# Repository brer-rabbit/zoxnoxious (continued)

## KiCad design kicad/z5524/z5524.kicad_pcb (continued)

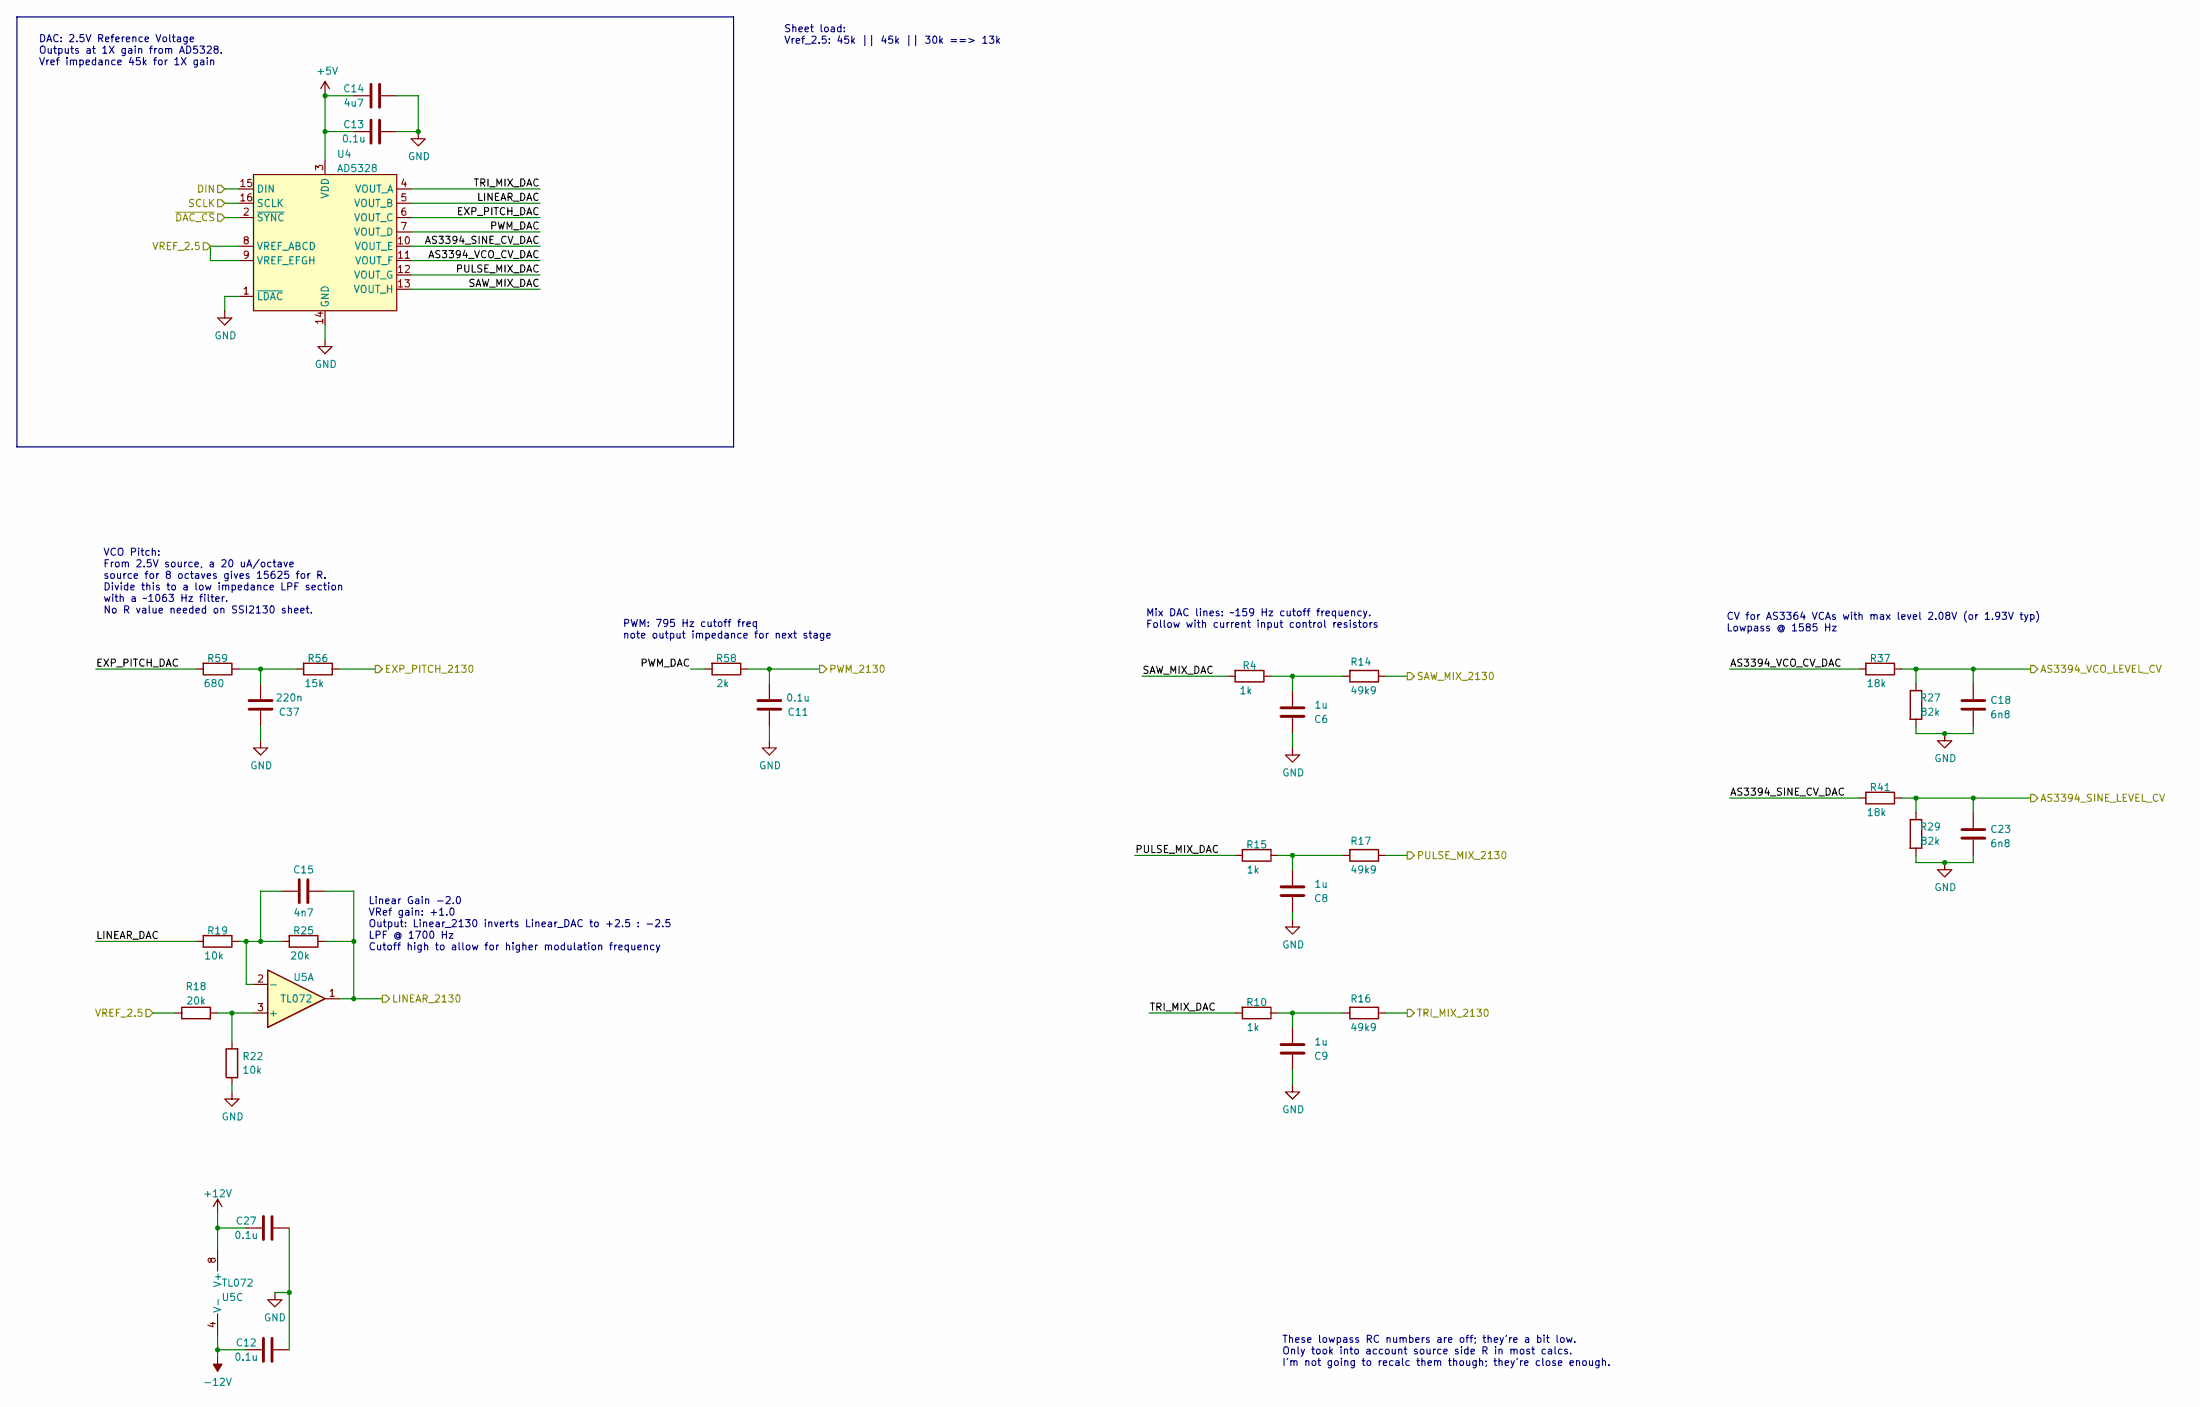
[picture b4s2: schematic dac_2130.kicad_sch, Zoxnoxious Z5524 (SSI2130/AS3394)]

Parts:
C6, C8, C9: 1u; C_0603_1608Metric; LCSC C15849
C11, C12, C13, C27: 0.1u; C_0603_1608Metric; LCSC C14663
C14: 4u7; C_0603_1608Metric; LCSC C19666
C15: 4n7; C_0603_1608Metric; LCSC C53987
C18, C23: 6n8; C_0603_1608Metric; LCSC C1631
C37: 220n; C_0603_1608Metric; LCSC C21120
R4, R10, R15: 1k; R_0603_1608Metric; LCSC C21190
R14, R16, R17: 49k9; R_0603_1608Metric; LCSC C23184
R18, R25: 20k; R_0603_1608Metric; LCSC C4184
R19, R22: 10k; R_0603_1608Metric; LCSC C25804
R27, R29: 82k; R_0603_1608Metric; LCSC C23254
R37, R41: 18k; R_0603_1608Metric; LCSC C25810
R56: 15k; R_0603_1608Metric; LCSC C22809
R58: 2k; R_0603_1608Metric; LCSC C22975
R59: 680; R_0603_1608Metric; LCSC C23228
U4: AD5328; TSSOP-16_4.4x5mm_P0.65mm; LCSC C29162
U5: TL072; SO-8_3.9x4.9mm_P1.27mm; LCSC C6961

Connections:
+5V: C13.1, C14.1, U4.3 (VDD); also elsewhere on the board
+12V: C27.1, U5.8 (V+); also elsewhere on the board
-12V: C12.1, U5.4 (V-); also elsewhere on the board
/AS3394_MOD_CV: C18.1, R27.1, R37.1; also elsewhere on the board
/AS3394_SINE_CV: C23.1, R29.1, R41.1; also elsewhere on the board
/DAC 2130/AS3394_SINE_CV_DAC: R41.2, U4.10 (VOUT_E)
/DAC 2130/AS3394_VCO_CV_DAC: R37.2, U4.11 (VOUT_F)
/DAC 2130/EXP_PITCH_2130: R56.1; also elsewhere on the board
/DAC 2130/EXP_PITCH_DAC: R59.2, U4.6 (VOUT_C)
/DAC 2130/LINEAR_2130: C15.2, R25.1, U5.1; also elsewhere on the board
/DAC 2130/LINEAR_DAC: R19.2, U4.5 (VOUT_B)
/DAC 2130/PULSE_MIX_2130: R17.1; also elsewhere on the board
/DAC 2130/PULSE_MIX_DAC: R15.2, U4.12 (VOUT_G)
/DAC 2130/PWM_2130: C11.1, R58.1; also elsewhere on the board
/DAC 2130/PWM_DAC: R58.2, U4.7 (VOUT_D)
/DAC 2130/SAW_MIX_2130: R14.1; also elsewhere on the board
/DAC 2130/SAW_MIX_DAC: R4.2, U4.13 (VOUT_H)
/DAC 2130/TRI_MIX_2130: R16.1; also elsewhere on the board
/DAC 2130/TRI_MIX_DAC: R10.2, U4.4 (VOUT_A)
/SPI_CLK: U4.16 (SCLK); also elsewhere on the board
/SPI_CS1: U4.2 (~SYNC); also elsewhere on the board
/SPI_MOSI: U4.15 (DIN); also elsewhere on the board
/VREF_2.5: R18.1, U4.8 (VREF_ABCD), U4.9 (VREF_EFGH); also elsewhere on the board
GND: C6.2, C8.2, C9.2, C11.2, C12.2, C13.2, C14.2, C18.2, C23.2, C27.2, C37.2, R22.1, R27.2, R29.2, U4.1 (~LDAC), U4.14 (GND); also elsewhere on the board
unnamed: C6.1, R4.1, R14.2
unnamed: C8.1, R15.1, R17.2
unnamed: C9.1, R10.1, R16.2
unnamed: C37.1, R56.2, R59.1
unnamed: R18.2, R22.2, U5.3 (+)
unnamed: C15.1, R19.1, R25.2, U5.2 (-)

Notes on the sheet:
PWM: 795 Hz cutoff freq note output impedance for next stage
Linear Gain -2.0 VRef gain: +1.0 Output: Linear_2130 inverts Linear_DAC to +2.5 : -2.5 LPF @ 1700 Hz Cutoff high to allow for higher modulation frequency
Mix DAC lines: ~159 Hz cutoff frequency. Follow with current input control resistors
These lowpass RC numbers are off; they're a bit low. Only took into account source side R in most calcs. I'm not going to recalc them though; they're close enough.
CV for AS3364 VCAs with max level 2.08V (or 1.93V typ) Lowpass @ 1585 Hz
VCO Pitch: From 2.5V source, a 20 uA/octave source for 8 octaves gives 15625 for R. Divide this to a low impedance LPF section with a ~1063 Hz filter. No R value needed on SSI2130 sheet.
Sheet load: Vref_2.5: 45k || 45k || 30k ==> 13k
DAC: 2.5V Reference Voltage Outputs at 1X gain from AD5328. Vref impedance 45k for 1X gain

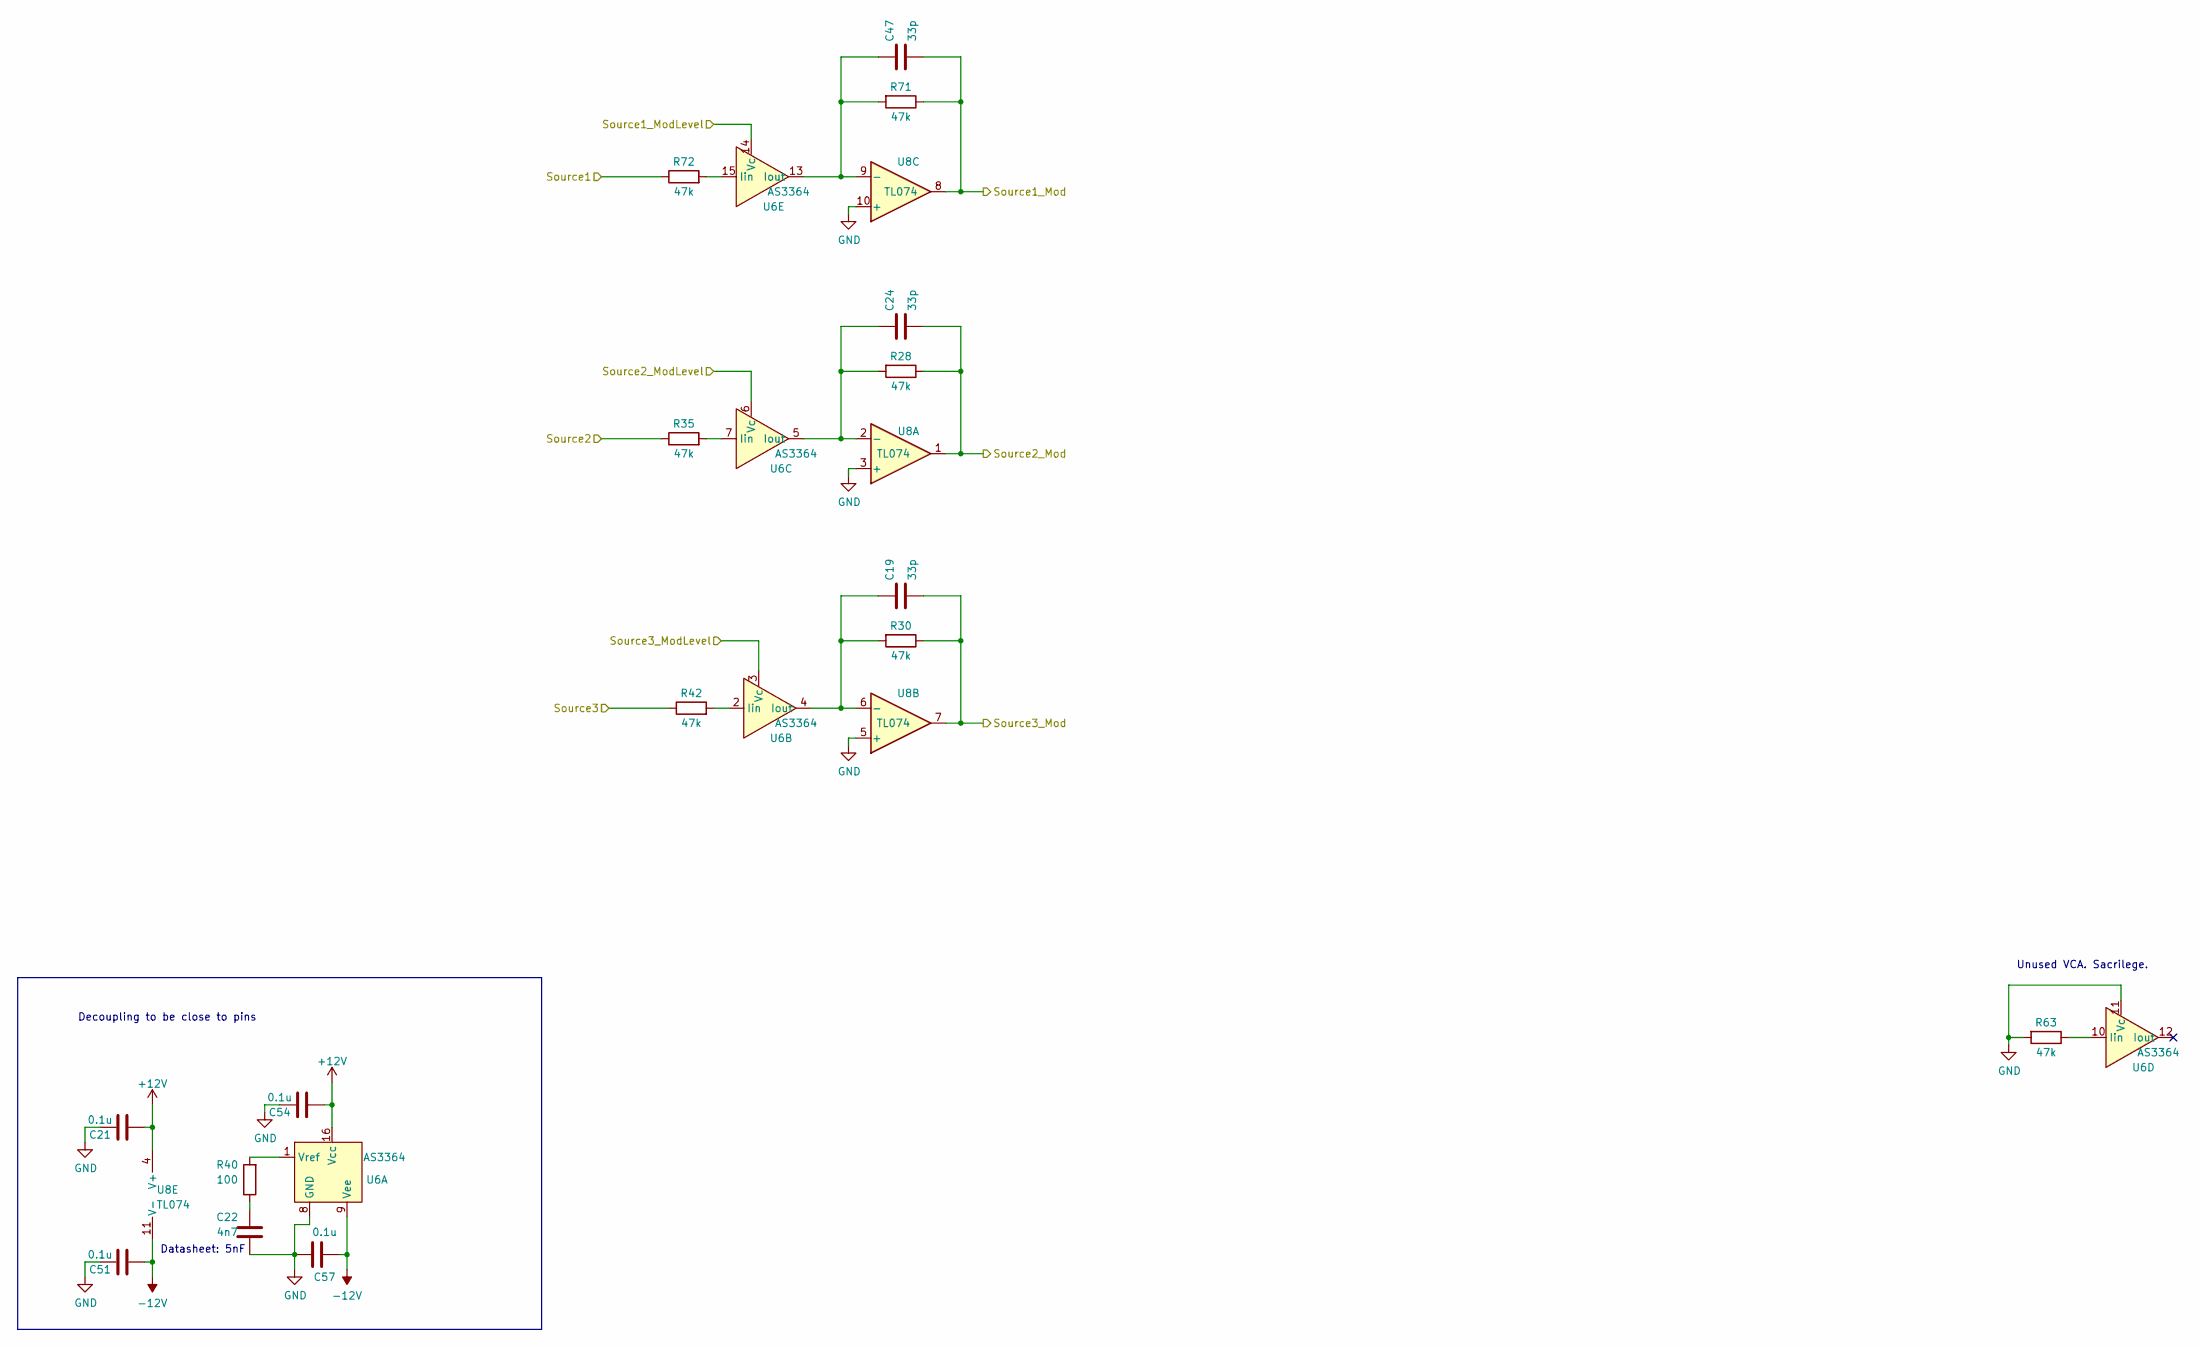
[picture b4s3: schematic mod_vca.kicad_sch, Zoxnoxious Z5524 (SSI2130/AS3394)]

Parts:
C19, C24, C47: 33p; C_0603_1608Metric; LCSC C1663
C21, C51, C54, C57: 0.1u; C_0603_1608Metric; LCSC C14663
C22: 4n7; C_0603_1608Metric; LCSC C53987
R28, R30, R35, R42, R63, R71, R72: 47k; R_0603_1608Metric; LCSC C25819
R40: 100; R_0603_1608Metric; LCSC C22775
U6: AS3364; SOIC-16_3.9x9.9mm_P1.27mm
U8: TL074; TSSOP-14_4.4x5mm_P0.65mm; LCSC C96507

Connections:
+12V: C21.1, C54.1, U6.16 (Vcc), U8.4 (V+); also elsewhere on the board
-12V: C51.1, C57.1, U6.9 (Vee), U8.11 (V-); also elsewhere on the board
/AS3394_MOD: C24.2, R28.1, U8.1; also elsewhere on the board
/AS3394_MOD_CV: U6.6 (Vc); also elsewhere on the board
/AS3394_SINE: R42.1; also elsewhere on the board
/AS3394_SINE_CV: U6.3 (Vc); also elsewhere on the board
/AS3394_SINE_MOD: C19.2, R30.1, U8.7; also elsewhere on the board
/Mod_VCA/Source2: R35.1; also elsewhere on the board
/SSI2130_MOD: C47.2, R71.1, U8.8; also elsewhere on the board
/SSI2130_MOD_CV: U6.14 (Vc); also elsewhere on the board
/SSI2130_VCO: R72.1; also elsewhere on the board
GND: C21.2, C22.2, C51.2, C54.2, C57.2, R63.2, U6.8 (GND), U6.11 (Vc), U8.3 (+), U8.5 (+), U8.10 (+); also elsewhere on the board
unnamed: C22.1, R40.1
unnamed: R40.2, U6.1 (Vref)
unnamed: R42.2, U6.2 (Iin)
unnamed: C19.1, R30.2, U6.4 (Iout), U8.6 (-)
unnamed: R35.2, U6.7 (Iin)
unnamed: C24.1, R28.2, U6.5 (Iout), U8.2 (-)
unnamed: R63.1, U6.10 (Iin)
unnamed: R72.2, U6.15 (Iin)
unnamed: C47.1, R71.2, U6.13 (Iout), U8.9 (-)

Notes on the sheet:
Unused VCA. Sacrilege.
Datasheet: 5nF
Decoupling to be close to pins

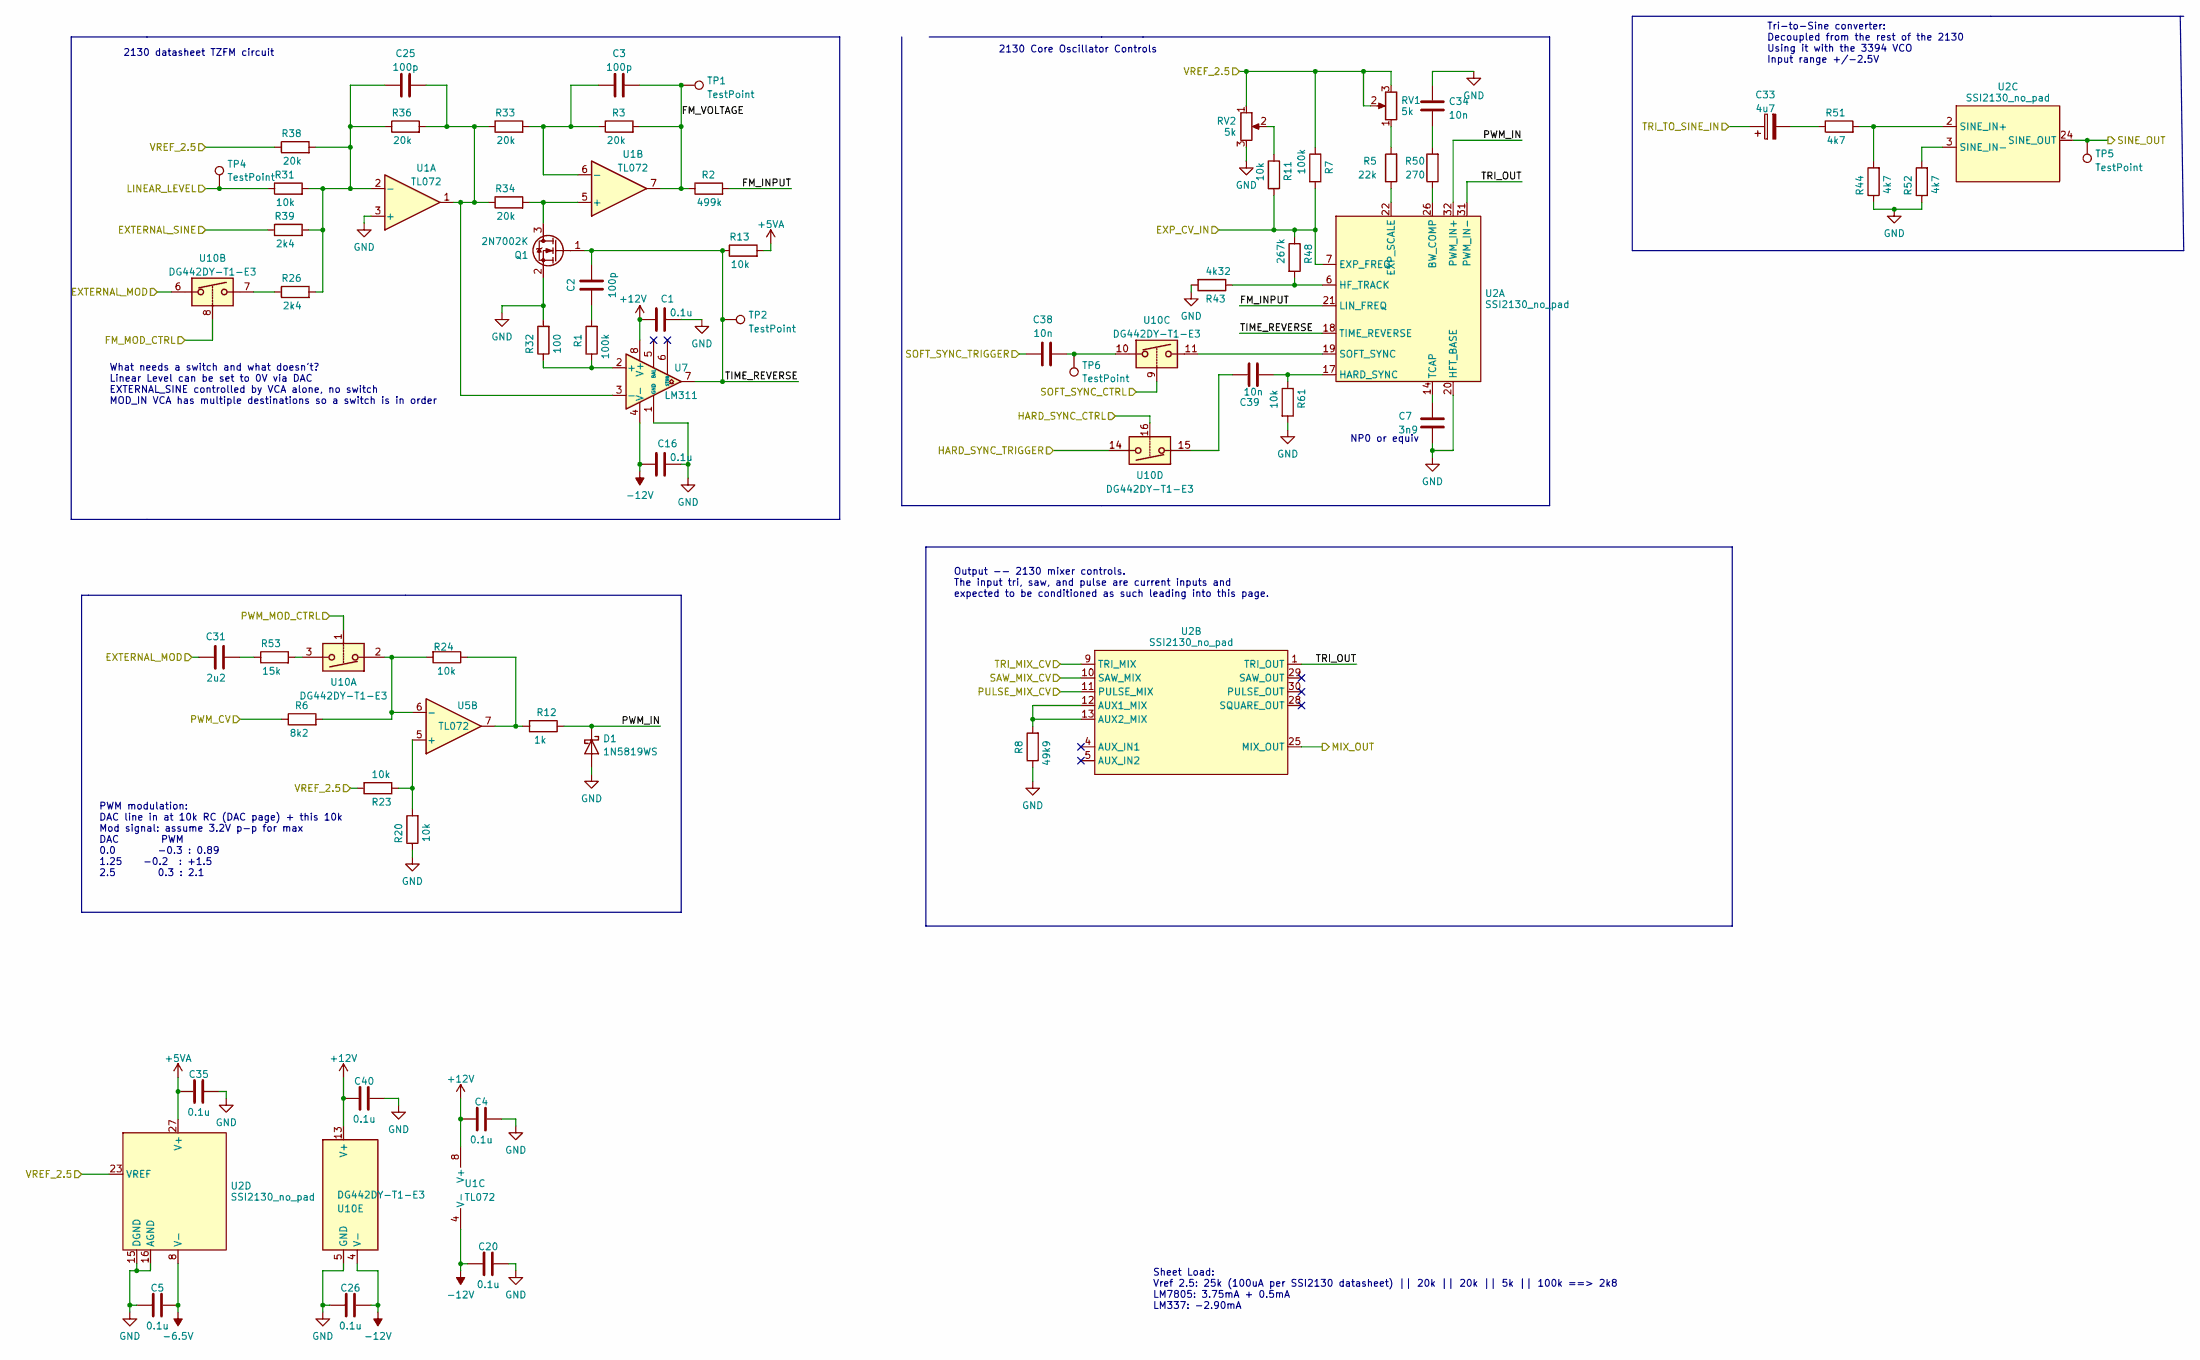
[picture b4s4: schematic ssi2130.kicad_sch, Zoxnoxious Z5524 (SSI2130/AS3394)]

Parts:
C1, C4, C5, C16, C20, C26, C35, C40: 0.1u; C_0603_1608Metric; LCSC C14663
C2, C3, C25: 100p; C_0603_1608Metric; LCSC C14858
C7: 3n9; C_0805_2012Metric; LCSC C541576
C31: 2u2; C_0603_1608Metric; LCSC C23630
C33: 4u7; CP_Radial_D4.0mm_P2.00mm; Digikey 1189-4115-ND
C34, C38, C39: 10n; C_0603_1608Metric; LCSC C57112
D1: 1N5819WS; D_SOD-323; LCSC C191023
Q1: 2N7002K; SOT-23; LCSC C8545
R1, R7: 100k; R_0603_1608Metric; LCSC C25803
R2: 499k; R_0603_1608Metric; LCSC C375514
R3, R33, R34, R36, R38: 20k; R_0603_1608Metric; LCSC C4184
R5: 22k; R_0603_1608Metric; LCSC C31850
R6: 8k2; R_0603_1608Metric; LCSC C25981
R8: 49k9; R_0603_1608Metric; LCSC C23184
R11, R13, R20, R23, R24, R31, R61: 10k; R_0603_1608Metric; LCSC C25804
R12: 1k; R_0603_1608Metric; LCSC C21190
R26, R39: 2k4; R_0603_1608Metric; LCSC C22940
R32: 100; R_0603_1608Metric; LCSC C22775
R43: 4k32; R_0603_1608Metric; LCSC C23158
R44, R51, R52: 4k7; R_0603_1608Metric; LCSC C23162
R48: 267k; R_0603_1608Metric; LCSC C22963
R50: 270; R_0603_1608Metric; LCSC C22966
R53: 15k; R_0603_1608Metric; LCSC C22809
RV1, RV2: 5k; Potentiometer_Bourns_3296W_Vertical
TP1, TP2, TP4, TP5, TP6: TestPoint; TestPoint_Pad_1.5x1.5mm
U1, U5: TL072; SO-8_3.9x4.9mm_P1.27mm; LCSC C6961
U2: SSI2130_no_pad; QFN-32-1EP_4x4mm_P0.4mm_EP2.65x2.65mm_Handsolder_NoPad
U7: LM311; TSSOP-8_4.4x3mm_P0.65mm; LCSC C2876875
U10: DG442DY-T1-E3; SOIC-16_3.9x9.9mm_P1.27mm; LCSC C2673321

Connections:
+5VA: C35.1, R13.2, U2.27 (V+); also elsewhere on the board
+12V: C1.1, C4.1, C40.1, U1.8 (V+), U7.8 (V+), U10.13 (V+); also elsewhere on the board
-6V: C5.2, U2.8 (V-); also elsewhere on the board
-12V: C16.1, C20.2, C26.2, U1.4 (V-), U7.4 (V-), U10.4 (V-); also elsewhere on the board
/AS3394_MOD: C31.1, U10.6; also elsewhere on the board
/AS3394_SINE: TP5.1, U2.24 (SINE_OUT); also elsewhere on the board
/AS3394_SINE_MOD: R39.1; also elsewhere on the board
/AS3394_VCO: C33.1; also elsewhere on the board
/DAC 2130/EXP_PITCH_2130: R7.2, R11.2, R48.1, U2.7 (EXP_FREQ); also elsewhere on the board
/DAC 2130/LINEAR_2130: R31.1, TP4.1; also elsewhere on the board
/DAC 2130/PULSE_MIX_2130: U2.11 (PULSE_MIX); also elsewhere on the board
/DAC 2130/PWM_2130: R6.1; also elsewhere on the board
/DAC 2130/SAW_MIX_2130: U2.10 (SAW_MIX); also elsewhere on the board
/DAC 2130/TRI_MIX_2130: U2.9 (TRI_MIX); also elsewhere on the board
/FM2130_MOD_CTRL: U10.8; also elsewhere on the board
/HARDSYNC_2130_CTRL: U10.16; also elsewhere on the board
/HARD_SYNC_SOURCE: U10.14; also elsewhere on the board
/PWM2130_MOD_CTRL: U10.1; also elsewhere on the board
/SOFTSYNC_2130_CTRL: U10.9; also elsewhere on the board
/SOFT_SYNC_SOURCE: C38.1; also elsewhere on the board
/SSI2130/FM_INPUT: R2.2, U2.21 (LIN_FREQ)
/SSI2130/FM_VOLTAGE: C3.2, R2.1, R3.2, TP1.1, U1.7
/SSI2130/MIX_OUT: U2.25 (MIX_OUT); also elsewhere on the board
/SSI2130/PWM_IN: D1.1 (K), R12.1, U2.32 (PWM_IN+)
/SSI2130/TIME_REVERSE: C2.2, Q1.1 (G), R13.1, TP2.1, U2.18 (TIME_REVERSE), U7.7
/SSI2130/TRI_OUT: U2.1 (TRI_OUT), U2.31 (PWM_IN-)
/VREF_2.5: R7.1, R23.2, R38.1, RV1.2, RV1.3, RV2.1, U2.23 (VREF); also elsewhere on the board
GND: C1.2, C4.2, C5.1, C7.2, C16.2, C20.1, C26.1, C34.1, C35.2, C40.2, D1.2 (A), Q1.2 (S), R8.1, R20.1, R32.2, R43.2, R44.1, R52.1, R61.2, RV2.3, U1.3 (+), U2.15 (DGND), U2.16 (AGND), U2.20 (HFT_BASE), U7.1 (GND), U10.5 (GND); also elsewhere on the board
unnamed: C2.1, R1.2
unnamed: C31.2, R53.1
unnamed: C33.2, R51.1
unnamed: C34.2, R50.2
unnamed: C38.2, TP6.1, U10.10
unnamed: C39.1, U10.15
unnamed: Q1.3 (D), R34.2, U1.5 (+)
unnamed: R5.2, RV1.1
unnamed: R11.1, RV2.2
unnamed: R12.2, R24.1, U5.7
unnamed: R26.1, U10.7
unnamed: R53.2, U10.3
unnamed: C25.1, R26.2, R31.2, R36.1, R38.2, R39.2, U1.2 (-)
unnamed: C3.1, R3.1, R33.2, U1.6 (-)
unnamed: R50.1, U2.26 (BW_COMP)
unnamed: R5.1, U2.22 (EXP_SCALE)
unnamed: C39.2, R61.1, U2.17 (HARD_SYNC)
unnamed: R43.1, R48.2, U2.6 (HF_TRACK)
unnamed: U2.19 (SOFT_SYNC), U10.11
unnamed: C7.1, U2.14 (TCAP)
unnamed: R8.2, U2.12 (AUX1_MIX), U2.13 (AUX2_MIX)
unnamed: R44.2, R51.2, U2.2 (SINE_IN+)
unnamed: R52.2, U2.3 (SINE_IN-)
unnamed: R20.2, R23.1, U5.5 (+)
unnamed: R6.2, R24.2, U5.6 (-), U10.2
unnamed: R1.1, R32.1, U7.2 (+)
unnamed: C25.2, R33.1, R34.1, R36.2, U1.1, U7.3 (-)

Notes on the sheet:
What needs a switch and what doesn't? Linear Level can be set to 0V via DAC EXTERNAL_SINE controlled by VCA alone, no switch MOD_IN VCA has multiple destinations so a switch is in order
PWM modulation: DAC line in at 10k RC (DAC page) + this 10k Mod signal: assume 3.2V p-p for max DAC PWM 0.0 -0.3 : 0.89 1.25 -0.2 : +1.5 2.5 0.3 : 2.1
Sheet Load: Vref 2.5: 25k (100uA per SSI2130 datasheet) || 20k || 20k || 5k || 100k ==> 2k8 LM7805: 3.75mA + 0.5mA LM337: -2.90mA
2130 Core Oscillator Controls
2130 datasheet TZFM circuit
NP0 or equiv
Output -- 2130 mixer controls. The input tri, saw, and pulse are current inputs and expected to be conditioned as such leading into this page.
Tri-to-Sine converter: Decoupled from the rest of the 2130 Using it with the 3394 VCO Input range +/-2.5V

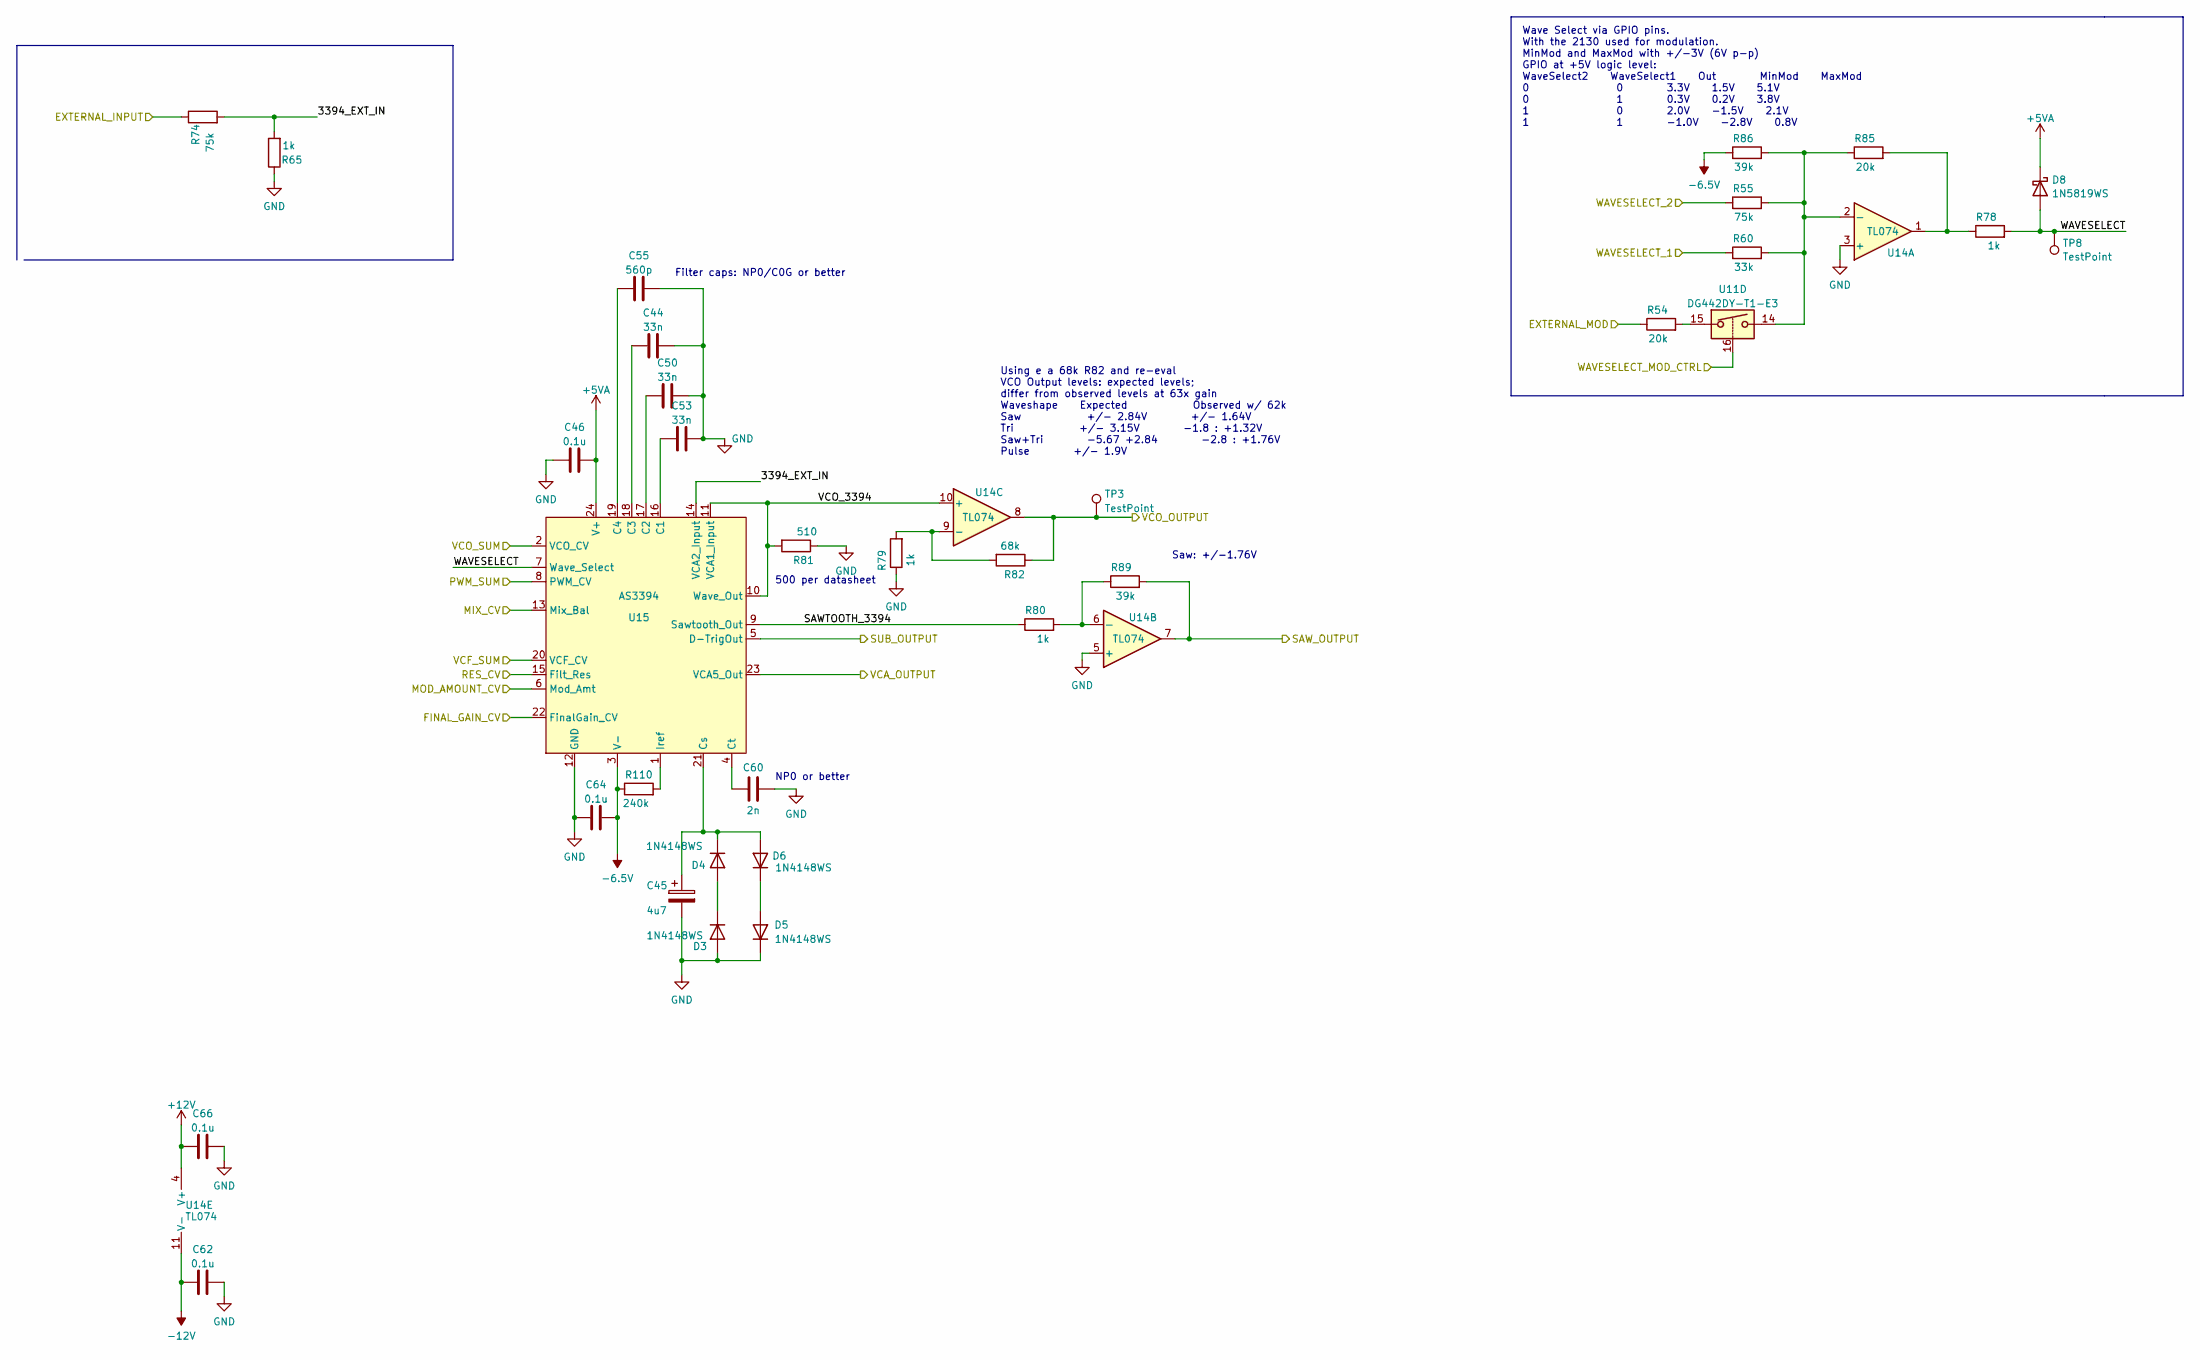
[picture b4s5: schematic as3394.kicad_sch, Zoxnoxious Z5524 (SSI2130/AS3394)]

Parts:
C44, C50, C53: 33n; C_0805_2012Metric; Digikey 445-7523-1-ND
C45: 4u7; CP_Radial_D4.0mm_P2.00mm; Digikey 1189-4115-ND
C46, C62, C64, C66: 0.1u; C_0603_1608Metric; LCSC C14663
C55: 560p; C_0603_1608Metric; LCSC C458906
C60: 2n; C_1206_3216Metric; Digikey C1206X202FBGAC7800
D3, D4, D5, D6: 1N4148WS; D_SOD-323; LCSC C2128
D8: 1N5819WS; D_SOD-323; LCSC C191023
R54, R85: 20k; R_0603_1608Metric; LCSC C4184
R55, R74: 75k; R_0603_1608Metric; LCSC C23242
R60: 33k; R_0603_1608Metric; LCSC C4216
R65, R78, R79, R80: 1k; R_0603_1608Metric; LCSC C21190
R81: 510; R_0603_1608Metric; LCSC C23193
R82: 68k; R_0603_1608Metric; LCSC C23231
R86, R89: 39k; R_0603_1608Metric; LCSC C23153
R110: 240k; R_0603_1608Metric; LCSC C4197
TP3, TP8: TestPoint; TestPoint_Pad_1.5x1.5mm
U11: DG442DY-T1-E3; SOIC-16_3.9x9.9mm_P1.27mm; LCSC C2673321
U14: TL074; TSSOP-14_4.4x5mm_P0.65mm; LCSC C96507
U15: AS3394; SOIC-24W_7.5x15.4mm_P1.27mm

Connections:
+5VA: C46.2, D8.1 (K), U15.24 (V+); also elsewhere on the board
+12V: C66.1, U14.4 (V+); also elsewhere on the board
-6V: C64.2, R86.1, R110.1, U15.3 (V-); also elsewhere on the board
-12V: C62.1, U14.11 (V-); also elsewhere on the board
/AS3394/3394_EXT_IN: R65.2, R74.2, U15.14 (VCA2_Input)
/AS3394/FINAL_GAIN_CV: U15.22 (FinalGain_CV); also elsewhere on the board
/AS3394/MIX_CV: U15.13 (Mix_Bal); also elsewhere on the board
/AS3394/MOD_AMOUNT_CV: U15.6 (Mod_Amt); also elsewhere on the board
/AS3394/PWM_SUM: U15.8 (PWM_CV); also elsewhere on the board
/AS3394/RES_CV: U15.15 (Filt_Res); also elsewhere on the board
/AS3394/SAWTOOTH_3394: R80.1, U15.9 (Sawtooth_Out)
/AS3394/VCA_OUTPUT: U15.23 (VCA5_Out); also elsewhere on the board
/AS3394/VCF_SUM: U15.20 (VCF_CV); also elsewhere on the board
/AS3394/VCO_3394: R81.2, U14.10 (+), U15.10 (Wave_Out), U15.11 (VCA1_Input)
/AS3394/VCO_SUM: U15.2 (VCO_CV); also elsewhere on the board
/AS3394/WAVESELECT: D8.2 (A), R78.2, TP8.1, U15.7 (Wave_Select)
/AS3394_VCO: R82.1, TP3.1, U14.8; also elsewhere on the board
/HARD_SYNC_SOURCE: U15.5 (D-TrigOut); also elsewhere on the board
/SOFT_SYNC_SOURCE: R89.2, U14.7; also elsewhere on the board
/SSI2130_MOD: R54.1; also elsewhere on the board
/SSI2130_VCO: R74.1; also elsewhere on the board
/WAVESELECT_1: R60.1; also elsewhere on the board
/WAVESELECT_2: R55.1; also elsewhere on the board
/WAVESELECT_MOD_CTRL: U11.16; also elsewhere on the board
GND: C44.2, C45.2, C46.1, C50.2, C53.2, C55.2, C60.2, C62.2, C64.1, C66.2, D3.2 (A), D5.1 (K), R65.1, R79.1, R81.1, U14.3 (+), U14.5 (+), U15.12 (GND); also elsewhere on the board
unnamed: D3.1 (K), D4.2 (A)
unnamed: C45.1, D4.1 (K), D6.2 (A), U15.21 (Cs)
unnamed: D5.2 (A), D6.1 (K)
unnamed: R54.2, U11.15
unnamed: R78.1, R85.2, U14.1
unnamed: R55.2, R60.2, R85.1, R86.2, U11.14, U14.2 (-)
unnamed: R80.2, R89.1, U14.6 (-)
unnamed: R79.2, R82.2, U14.9 (-)
unnamed: C53.1, U15.16 (C1)
unnamed: C50.1, U15.17 (C2)
unnamed: C44.1, U15.18 (C3)
unnamed: C55.1, U15.19 (C4)
unnamed: C60.1, U15.4 (Ct)
unnamed: R110.2, U15.1 (Iref)

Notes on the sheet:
Wave Select via GPIO pins. With the 2130 used for modulation. MinMod and MaxMod with +/-3V (6V p-p) GPIO at +5V logic level: WaveSelect2 WaveSelect1 Out MinMod MaxMod 0 0 3.3V 1.5V 5.1V 0 1 0.3V 0.2V 3.8V 1 0 2.0V -1.5V 2.1V 1 1 -1.0V -2.8V 0.8V
NP0 or better
Saw: +/-1.76V
Using e a 68k R82 and re-eval VCO Output levels: expected levels; differ from observed levels at 63x gain Waveshape Expected Observed w/ 62k Saw +/- 2.84V +/- 1.64V Tri +/- 3.15V -1.8 : +1.32V Saw+Tri -5.67 +2.84 -2.8 : +1.76V Pulse +/- 1.9V
Filter caps: NP0/C0G or better
500 per datasheet
